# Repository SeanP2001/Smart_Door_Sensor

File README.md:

# Smart Door Sensor Project

## Table of Contents

* [Table of Contents](#table-of-contents)
* [Introduction](#introduction)
* [Brief](#brief)
* [Method of Operation](#method-of-operation)
  + [Setting up The Device](#setting-up-the-device)
  + [Using the Device](#using-the-device)
* [Circuitry](#circuitry)
  + [Full Schematic](#full-schematic)
  + [Veroboard Prototype](#veroboard-prototype)
  + [PCB](#pcb)
* [Further Work](#further-work)

## Introduction

This originally started as a university project, and I have continued to develop this idea in my spare time.

## Brief

This project is a smart door alarm for security in university accommodation and hotel rooms. When somebody enters the room, the buzzer will sound, or the device will email the user. This standalone device does not require a smart hub to operate.

## Method of Operation

### Setting up The Device

1. Plug the device into a phone charger and switch the charger on.

2. Open the Wi-Fi settings on your smartphone and wait for the “S.P.U.D Smart
   System” network to appear. Once it appears, connect to it.

3. Turn off mobile data on your phone.

4. Open your phone’s web browser and enter “192.168.1.1” into the address bar.

5. When the page loads, input the following information:
   • Wi-Fi SSID - The name of your Wi-Fi network
   • Wi-Fi Password - Often found on the back of your Wi-Fi router
   • Device Name - The name which you want to give the device e.g., “Front Door”
   • Email Address - The email address to send notifications to
   • Your Name - The name which you want to appear on the email notifications

6. Press “Submit” and check that the credentials displayed on the next page are
   correct.

7. Wait for the LED on the device to flash green and then turn off the device and
   turn it back on again.

8. Now your device is setup.

9. Attach the sensor to the back of the door. Peel the sticky back off the main
   body and stick it to the edge of the door. Stick the magnetic contact to the
   door frame, as close to the sensor as possible. (Image showing device
   attached to door)

10. Open the door ensuring that the device does not catch on the door.

### Using the Device

Switching either of the switches will alter the settings and cause the indicator LED to light (The colour of the LED shows which setting has changed).

| Indicator LED Colour | Meaning                 |
| -------------------- | ----------------------- |
| Blue                 | Buzzer ON               |
| Yellow               | Buzzer OFF              |
| Green                | Email Notifications ON  |
| Red                  | Email Notifications OFF |

Depending on the settings, the sensor will either buzz or send an email notification when the door is opened.

## Circuitry

### Full Schematic

### Veroboard Prototype

|  |  |
| ----------------------------------------- | ------------------------------------------ |

### PCB

|  |  |
| ---------------------------------- | --------------------------------- |

## Further Work

I will be working to re-design the board for this project. I want to use a latch to power the microcontroller when the door is opened and power it off once it has sent the email. This will reduce power consumption.

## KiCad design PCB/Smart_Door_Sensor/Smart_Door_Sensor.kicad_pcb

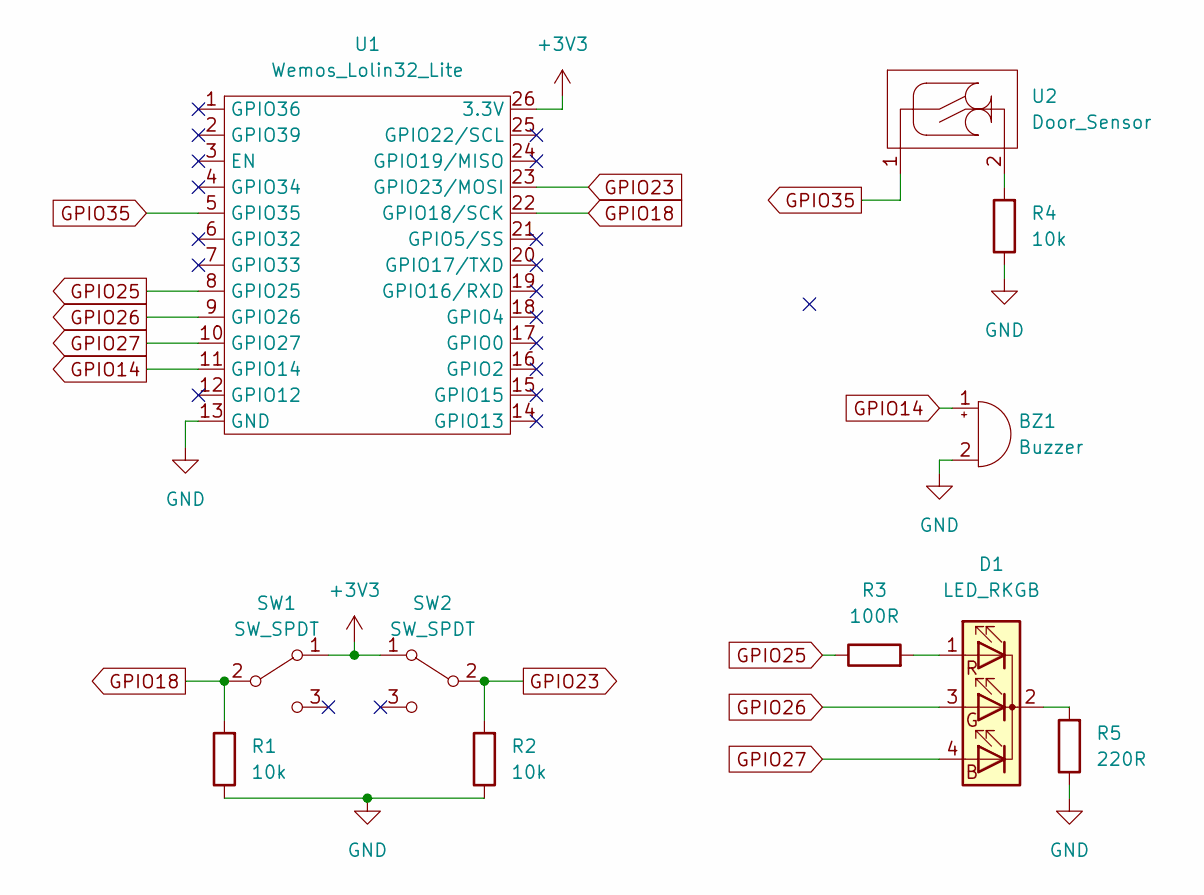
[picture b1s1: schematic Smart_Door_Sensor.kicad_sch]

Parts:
BZ1: Buzzer; MagneticBuzzer_ProSignal_ABT-410-RC
D1: LED_RKGB; LED_D5.0mm-4_RGB_Wide_Pins
R1, R2, R4: 10k; R_Axial_DIN0309_L9.0mm_D3.2mm_P12.70mm_Horizontal
R3: 100R; R_Axial_DIN0309_L9.0mm_D3.2mm_P12.70mm_Horizontal
R5: 220R; R_Axial_DIN0309_L9.0mm_D3.2mm_P12.70mm_Horizontal
SW1, SW2: SW_SPDT; SPDT_Slide_Switch
U1: Wemos_Lolin32_Lite
U2: Door_Sensor

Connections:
+3V3: SW1.1 (A), SW2.1 (A), U1.26 (3.3V)
GND: BZ1.2 (+), R1.1, R2.1, R4.1, R5.1, U1.13 (GND)
GPIO14: BZ1.1 (-), U1.11 (GPIO14)
GPIO18: R1.2, SW1.2 (B), U1.22 (GPIO18/SCK)
GPIO23: R2.2, SW2.2 (B), U1.23 (GPIO23/MOSI)
GPIO25: R3.1, U1.8 (GPIO25)
GPIO26: D1.3 (GA), U1.9 (GPIO26)
GPIO27: D1.4 (BA), U1.10 (GPIO27)
GPIO35: U1.5 (GPIO35), U2.1
unnamed: D1.1 (RA), R3.2
unnamed: D1.2 (K), R5.2
unnamed: R4.2, U2.2

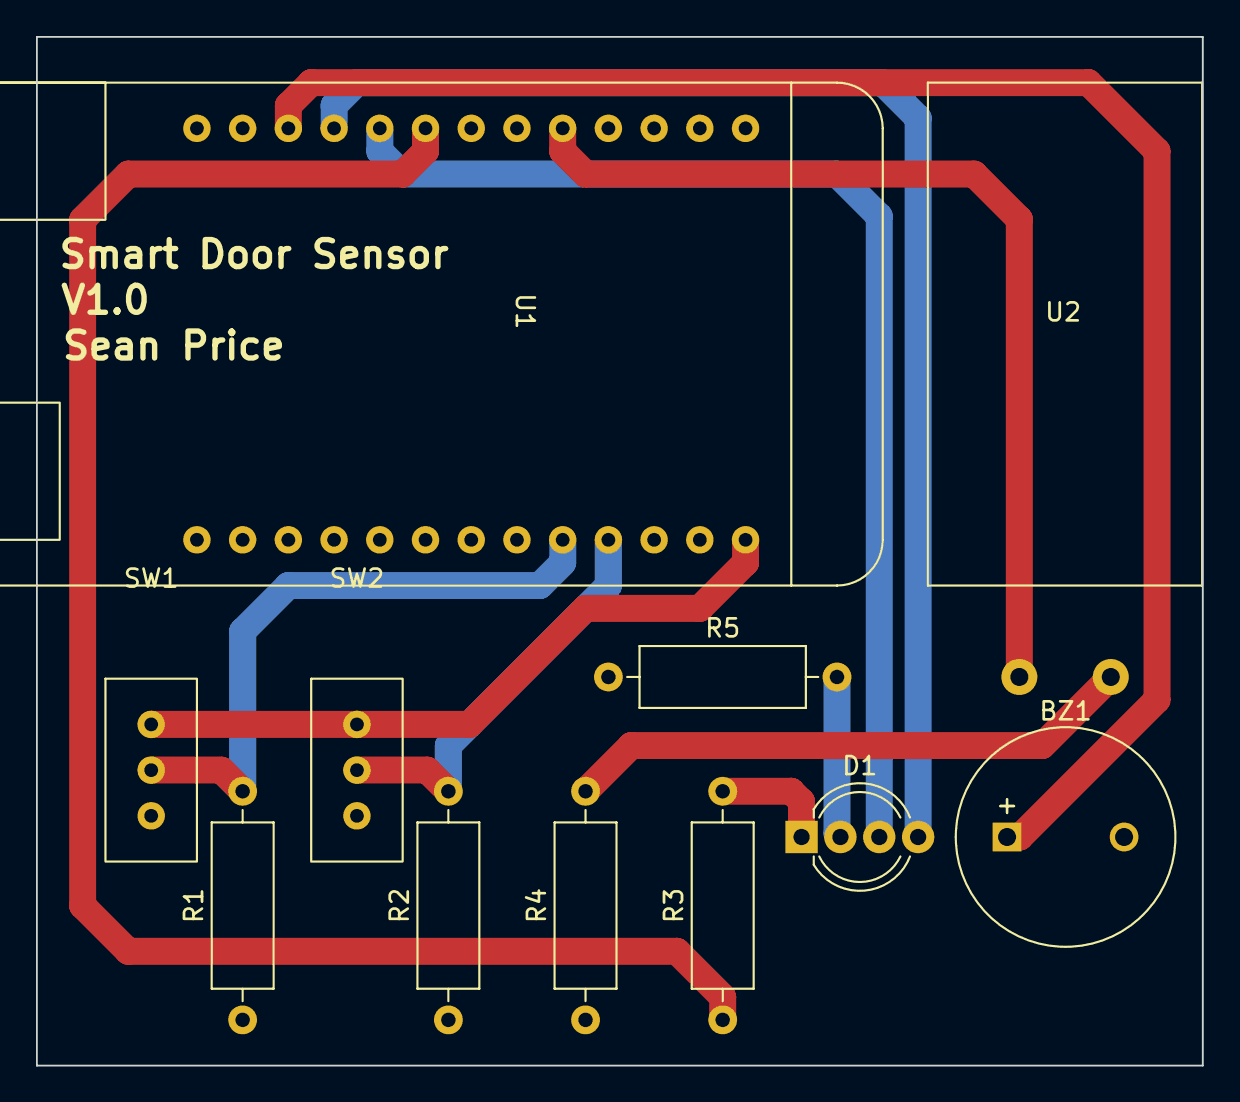
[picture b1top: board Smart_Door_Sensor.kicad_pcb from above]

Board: 2 copper layers, 64.8 x 57.2 mm, 11 parts (0 on the bottom side), 12 nets.

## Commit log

2021-11-22 V0.1 LED switches on and off in response to a reed switch
2021-11-22 V0.2 The device sends an email whenever the door is opened
2021-11-22 V0.3 Added saving details to EEPROM and loading details from EEPROM
2021-11-29 V0.4 Added buzzer, buzzer switch, email switch and RGB indicator LED
2021-12-01 V0.5 Added device setup via ESP32 access point
2022-05-29 V0.6 Designed PCB
2022-06-02 V0.6.1 Exported gerber files
2022-06-07 V0.6.2 Finalised PCB V1.0
2022-09-14 V0.6.3 Added LICENSE.md
2022-09-23 V0.6.4 Added Libraries
2022-09-23 V1.0.0 Updated README.md
